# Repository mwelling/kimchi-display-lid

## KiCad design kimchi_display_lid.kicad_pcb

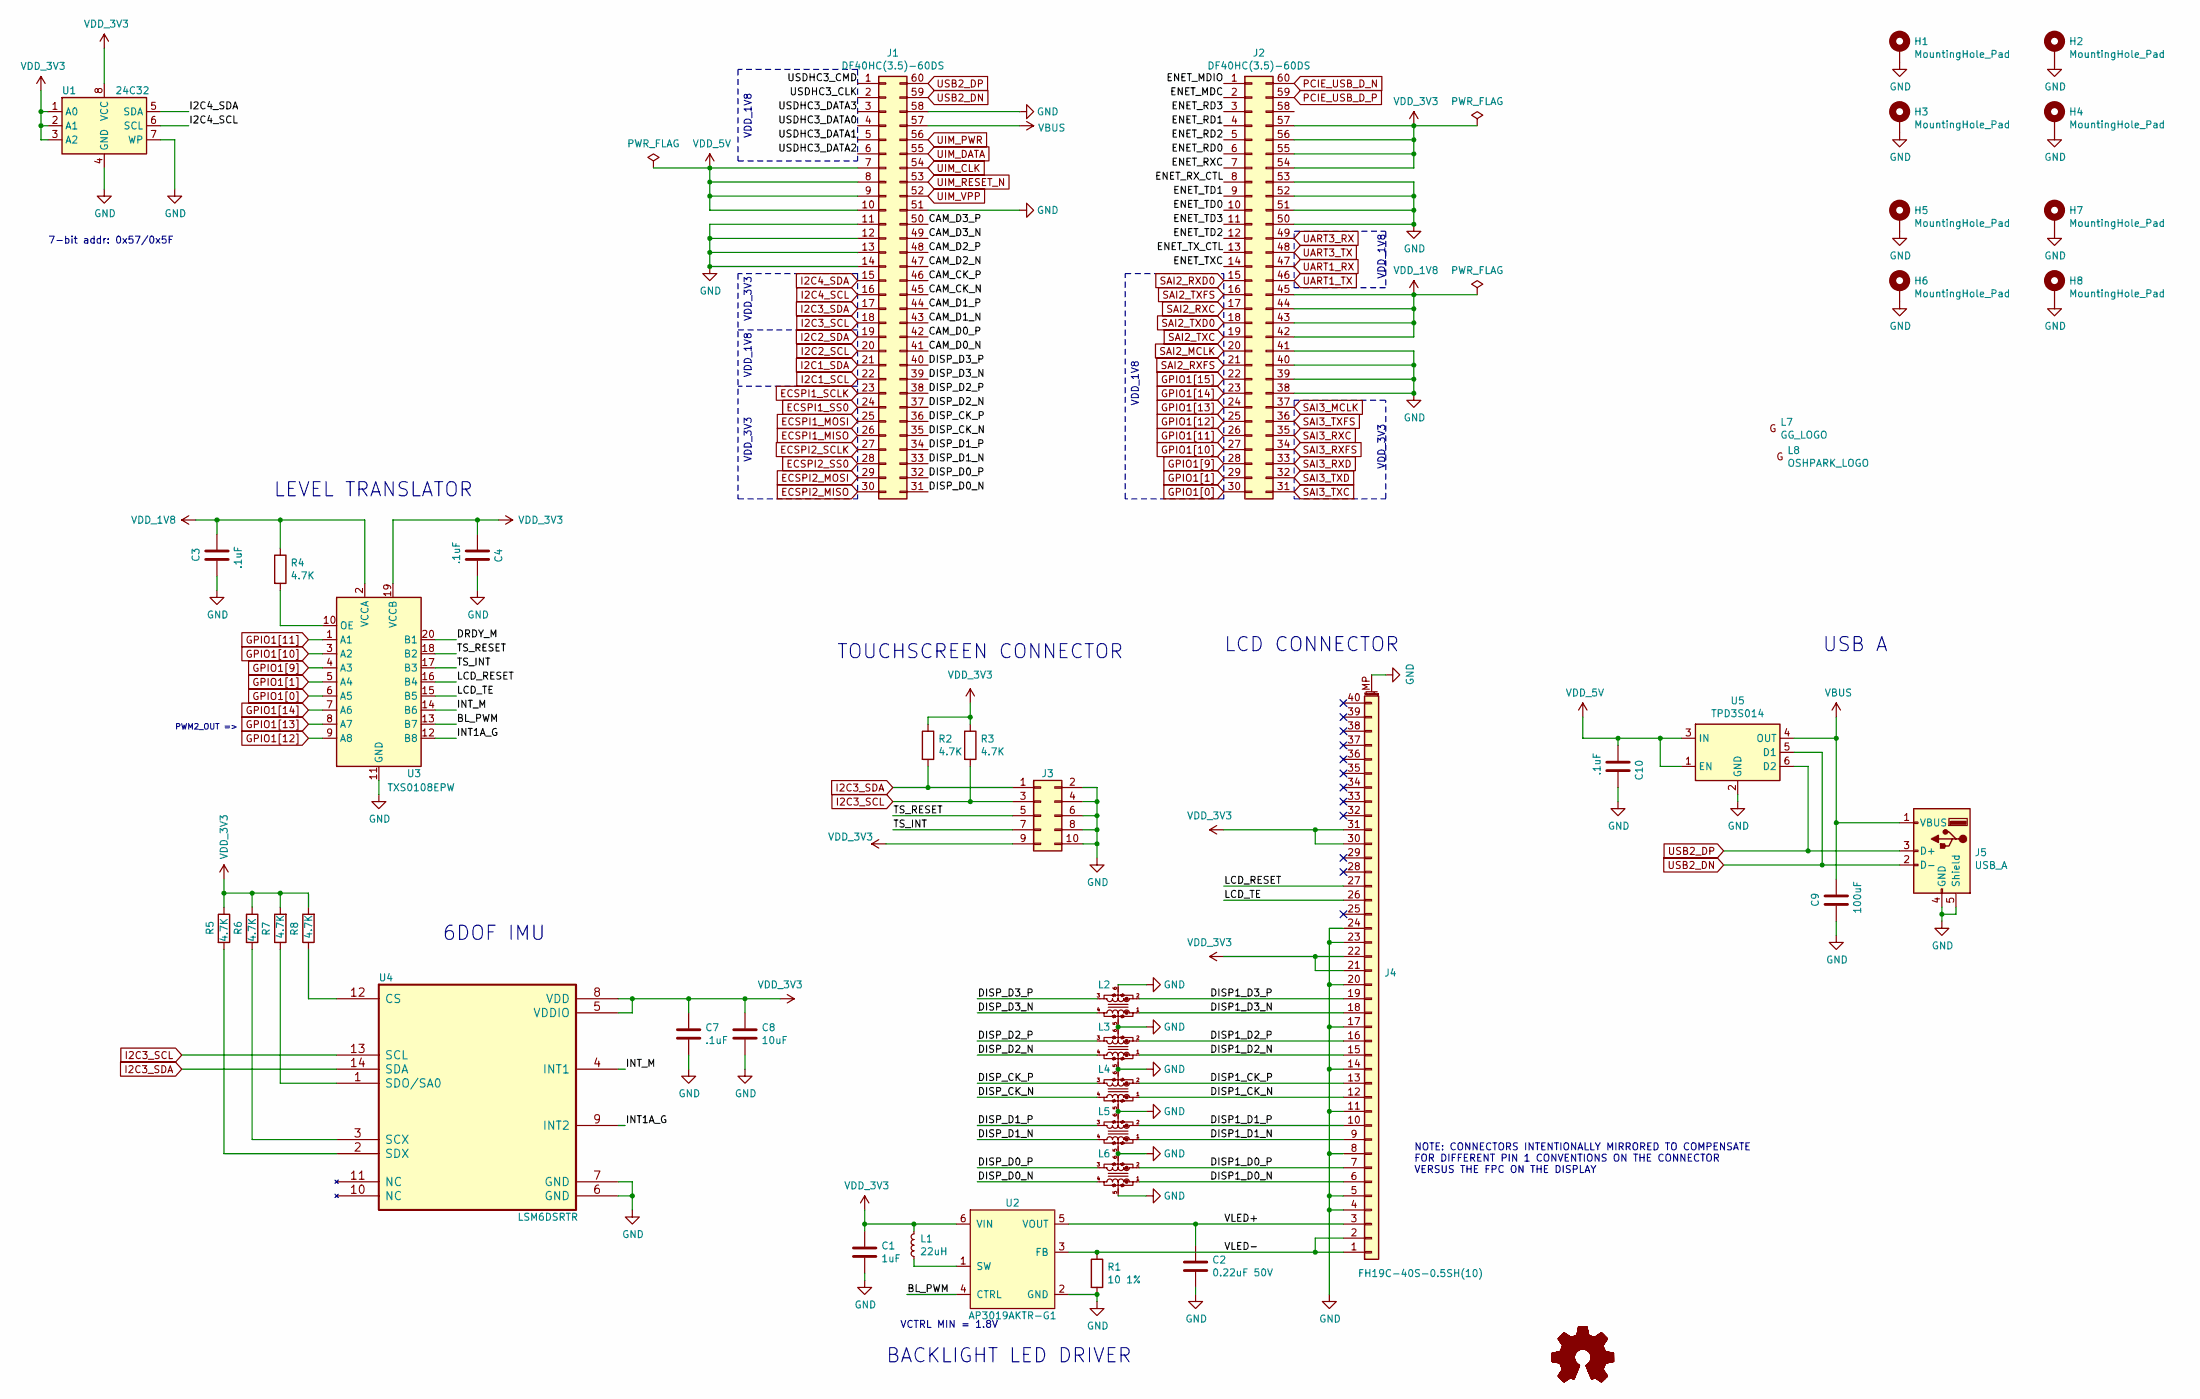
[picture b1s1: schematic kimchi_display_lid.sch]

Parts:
C1: 1uF; C_0603_1608Metric; Part C0603C105K4PAC7411
C2: 0.22uF 50V; C_0603_1608Metric; Part CGA3E3X7R1H224K080AB
C3, C4, C7, C10: .1uF; C_0603_1608Metric; Part C0603C104M5RACAUTO
C8: 10uF; C_0603_1608Metric; Part CL10A106MP8NNNC
C9: 100uF; C_1206_3216Metric; Part CC1206MKX5R5BB107
H1, H2, H3, H4, H5, H6, H7, H8: MountingHole_Pad; MountingHole_3mm_Pad
J1, J2: DF40HC(3.5)-60DS; Part DF40HC(3.5)-60DS
J3: Conn_02x05_Odd_Even; HIROSE_DF23C-10DS-0.5V(51)
J4: FH19C-40S-0.5SH(10); HRS_FH19C-40S-0.5SH_1x40-1MP_P0.50mm; Part FH19C-40S-0.5SH(10)
J5: USB_A; TE_1-292303-6; Part 1-292303-6
L1: 22uH; L_Taiyo-Yuden_MD-4040; Part TYA4012220M-10
L2, L3, L4, L5, L6: LCFE121002; Part LCFE121002
L7: GG_LOGO; groupgets_logo
L8: OSHPARK_LOGO; oshpark_logo
LOGO1: Logo_Open_Hardware_Small; OSHW-Logo_5.7x6mm_SilkScreen
LOGO2: Logo_Open_Hardware_Small; kimchi-micro-3d-model
LOGO3: Logo_Open_Hardware_Small; hoverboard-3d-model
R1: 10 1%; R_0603_1608Metric; Part RE0603FRE0710RL
R2, R3, R4, R5, R6, R7, R8: 4.7K; R_0603_1608Metric; Part RC0603JR-074K7L
U1: 24C32; DFN-8-1EP_3x2mm_P0.5mm_EP1.36x1.46mm; Part M24C32-FMC6TG
U2: AP3019AKTR-G1; SOT-23-6; Part AP3019AKTR-G1
U3: TXS0108EPW; TSSOP-20_4.4x6.5mm_P0.65mm; Part TXS0108EPW
U4: LSM6DSRTR
U5: TPD3S014; SOT-23-6; Part TPD3S014

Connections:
/BL_PWM: U2.4 (CTRL), U3.13 (B7)
/CAM_CK_N: J1.45
/CAM_CK_P: J1.46
/CAM_D0_N: J1.41
/CAM_D0_P: J1.42
/CAM_D1_N: J1.43
/CAM_D1_P: J1.44
/CAM_D2_N: J1.47
/CAM_D2_P: J1.48
/CAM_D3_N: J1.49
/CAM_D3_P: J1.50
/DISP1_CK_N: J4.12, L4.1
/DISP1_CK_P: J4.13, L4.2
/DISP1_D0_N: J4.6, L6.1
/DISP1_D0_P: J4.7, L6.2
/DISP1_D1_N: J4.9, L5.1
/DISP1_D1_P: J4.10, L5.2
/DISP1_D2_N: J4.15, L3.1
/DISP1_D2_P: J4.16, L3.2
/DISP1_D3_N: J4.18, L2.1
/DISP1_D3_P: J4.19, L2.2
/DISP_CK_N: J1.35, L4.4
/DISP_CK_P: J1.36, L4.3
/DISP_D0_N: J1.31, L6.4
/DISP_D0_P: J1.32, L6.3
/DISP_D1_N: J1.33, L5.4
/DISP_D1_P: J1.34, L5.3
/DISP_D2_N: J1.37, L3.4
/DISP_D2_P: J1.38, L3.3
/DISP_D3_N: J1.39, L2.4
/DISP_D3_P: J1.40, L2.3
/DRDY_M: U3.20 (B1)
/ENET_MDC: J2.2
/ENET_MDIO: J2.1
/ENET_RD0: J2.6
/ENET_RD1: J2.4
/ENET_RD2: J2.5
/ENET_RD3: J2.3
/ENET_RXC: J2.7
/ENET_RX_CTL: J2.8
/ENET_TD0: J2.10
/ENET_TD1: J2.9
/ENET_TD2: J2.12
/ENET_TD3: J2.11
/ENET_TXC: J2.14
/ENET_TX_CTL: J2.13
/INT1A_G: U3.12 (B8), U4.9 (INT2)
/INT_M: U3.14 (B6), U4.4 (INT1)
/LCD_RESET: J4.27, U3.16 (B4)
/LCD_TE: J4.26, U3.15 (B5)
/TS_INT: J3.7, U3.17 (B3)
/TS_RESET: J3.5, U3.18 (B2)
/USDHC3_CLK: J1.2
/USDHC3_CMD: J1.1
/USDHC3_DATA0: J1.4
/USDHC3_DATA1: J1.5
/USDHC3_DATA2: J1.6
/USDHC3_DATA3: J1.3
/VLED+: C2.1, J4.3, U2.5 (VOUT)
/VLED-: J4.1, J4.2, R1.1, U2.3 (FB)
ECSPI1_MISO: J1.26
ECSPI1_MOSI: J1.25
ECSPI1_SCLK: J1.23
ECSPI1_SS0: J1.24
ECSPI2_MISO: J1.30
ECSPI2_MOSI: J1.29
ECSPI2_SCLK: J1.27
ECSPI2_SS0: J1.28
GND: C1.2, C2.2, C3.2, C4.1, C7.2, C8.2, C9.2, C10.1, H1.1, H2.1, H3.1, H4.1, H5.1, H6.1, H7.1, H8.1, J1.11, J1.12, J1.13, J1.14, J1.51, J1.58, J2.38, J2.39, J2.40, J2.41, J2.50, J2.51, J2.52, J2.53, J3.2, J3.4, J3.6, J3.8, J3.10, J4.4, J4.5, J4.8, J4.11, J4.14, J4.17, J4.20, J4.23, J4.24, J4.MP (MountPin), J5.4 (GND), J5.5 (Shield), L2.5, L2.6 (5), L3.5, L3.6 (5), L4.5, L4.6 (5), L5.5, L5.6 (5), L6.5, L6.6 (5), R1.2, U1.4 (GND), U1.7 (WP), U2.2 (GND), U3.11 (GND), U4.6 (GND), U4.7 (GND), U5.2 (GND)
GPIO1[0]: J2.30, U3.6 (A5)
GPIO1[1]: J2.29, U3.5 (A4)
GPIO1[9]: J2.28, U3.4 (A3)
GPIO1[10]: J2.27, U3.3 (A2)
GPIO1[11]: J2.26, U3.1 (A1)
GPIO1[12]: J2.25, U3.9 (A8)
GPIO1[13]: J2.24, U3.8 (A7)
GPIO1[14]: J2.23, U3.7 (A6)
GPIO1[15]: J2.22
I2C1_SCL: J1.22
I2C1_SDA: J1.21
I2C2_SCL: J1.20
I2C2_SDA: J1.19
I2C3_SCL: J1.18, J3.3, R3.2, U4.13 (SCL)
I2C3_SDA: J1.17, J3.1, R2.2, U4.14 (SDA)
I2C4_SCL: J1.16, U1.6 (SCL)
I2C4_SDA: J1.15, U1.5 (SDA)
unnamed: L1.1, U2.1 (SW)
unnamed: R4.2, U3.10 (OE)
unnamed: R5.2, U4.2 (SDX)
unnamed: R6.2, U4.3 (SCX)
unnamed: R7.1, U4.1 (SDO/SA0)
unnamed: R8.1, U4.12 (CS)
PCIE_USB_D_N: J2.60
PCIE_USB_D_P: J2.59
SAI2_MCLK: J2.20
SAI2_RXC: J2.17
SAI2_RXD0: J2.15
SAI2_RXFS: J2.21
SAI2_TXC: J2.19
SAI2_TXD0: J2.18
SAI2_TXFS: J2.16
SAI3_MCLK: J2.37
SAI3_RXC: J2.35
SAI3_RXD: J2.33
SAI3_RXFS: J2.34
SAI3_TXC: J2.31
SAI3_TXD: J2.32
SAI3_TXFS: J2.36
UART1_RX: J2.47
UART1_TX: J2.46
UART3_RX: J2.49
UART3_TX: J2.48
UIM_CLK: J1.54
UIM_DATA: J1.55
UIM_PWR: J1.56
UIM_RESET_N: J1.53
UIM_VPP: J1.52
USB2_DN: J1.59, J5.2 (D-), U5.5 (D1)
USB2_DP: J1.60, J5.3 (D+), U5.6 (D2)
VBUS: C9.1, J1.57, J5.1 (VBUS), U5.4 (OUT)
VDD_1V8: C3.1, J2.42, J2.43, J2.44, J2.45, R4.1, U3.2 (VCCA)
VDD_3V3: C1.1, C4.2, C7.1, C8.1, J2.54, J2.55, J2.56, J2.57, J3.9, J4.21, J4.22, J4.30, J4.31, L1.2, R2.1, R3.1, R5.1, R6.1, R7.2, R8.2, U1.1 (A0), U1.2 (A1), U1.3 (A2), U1.8 (VCC), U2.6 (VIN), U3.19 (VCCB), U4.5 (VDDIO), U4.8 (VDD)
VDD_5V: C10.2, J1.7, J1.8, J1.9, J1.10, U5.1 (EN), U5.3 (IN)

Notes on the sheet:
7-bit addr: 0x57/0x5F
VDD_1V8
VDD_3V3
BACKLIGHT LED DRIVER
VCTRL MIN = 1.8V
TOUCHSCREEN CONNECTOR
LCD CONNECTOR
NOTE: CONNECTORS INTENTIONALLY MIRRORED TO COMPENSATE FOR DIFFERENT PIN 1 CONVENTIONS ON THE CONNECTOR VERSUS THE FPC ON THE DISPLAY
LEVEL TRANSLATOR
PWM2_OUT =>
USB A
6DOF IMU

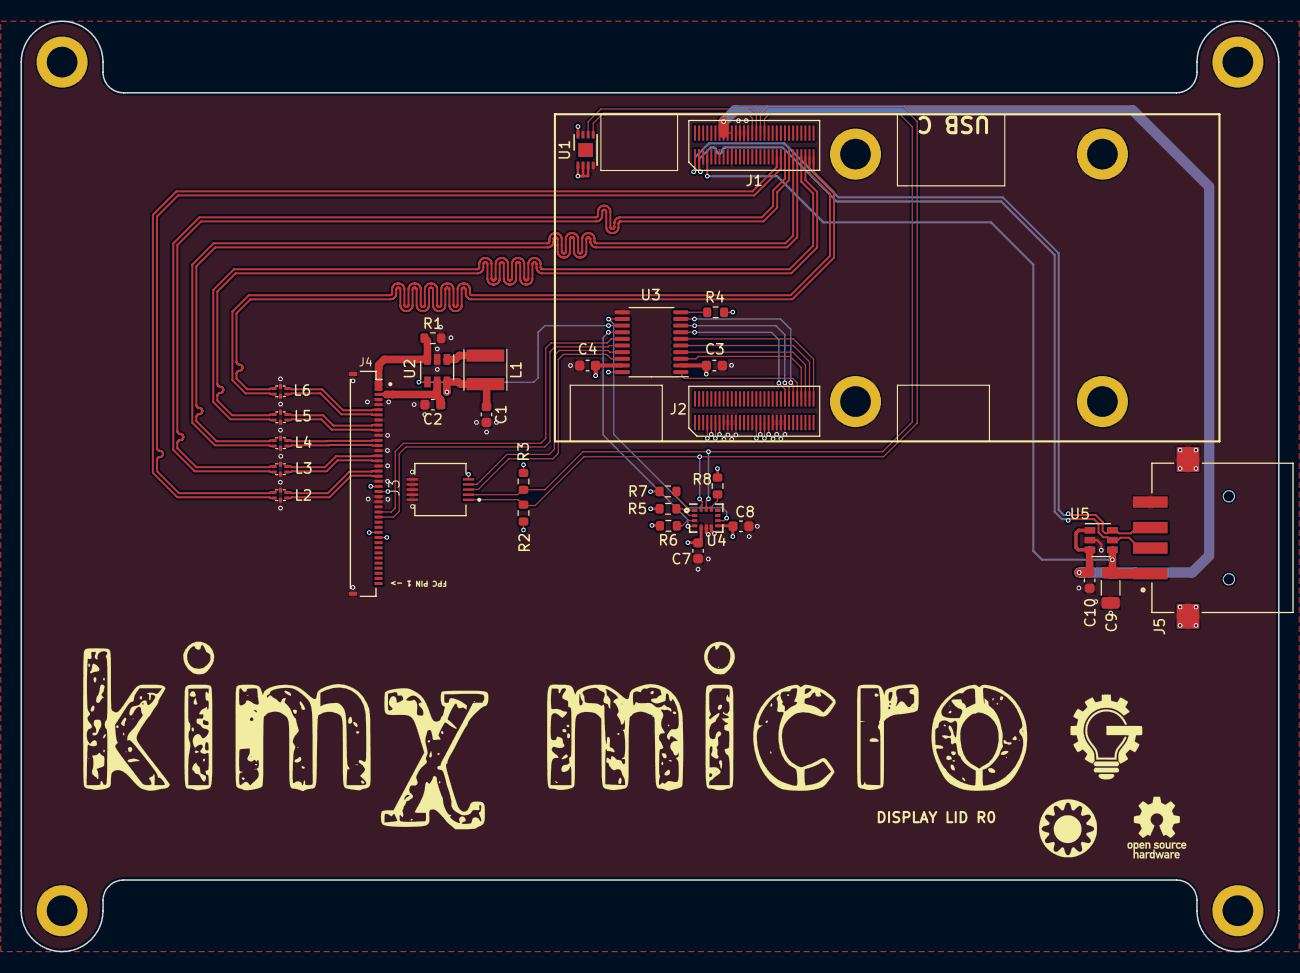
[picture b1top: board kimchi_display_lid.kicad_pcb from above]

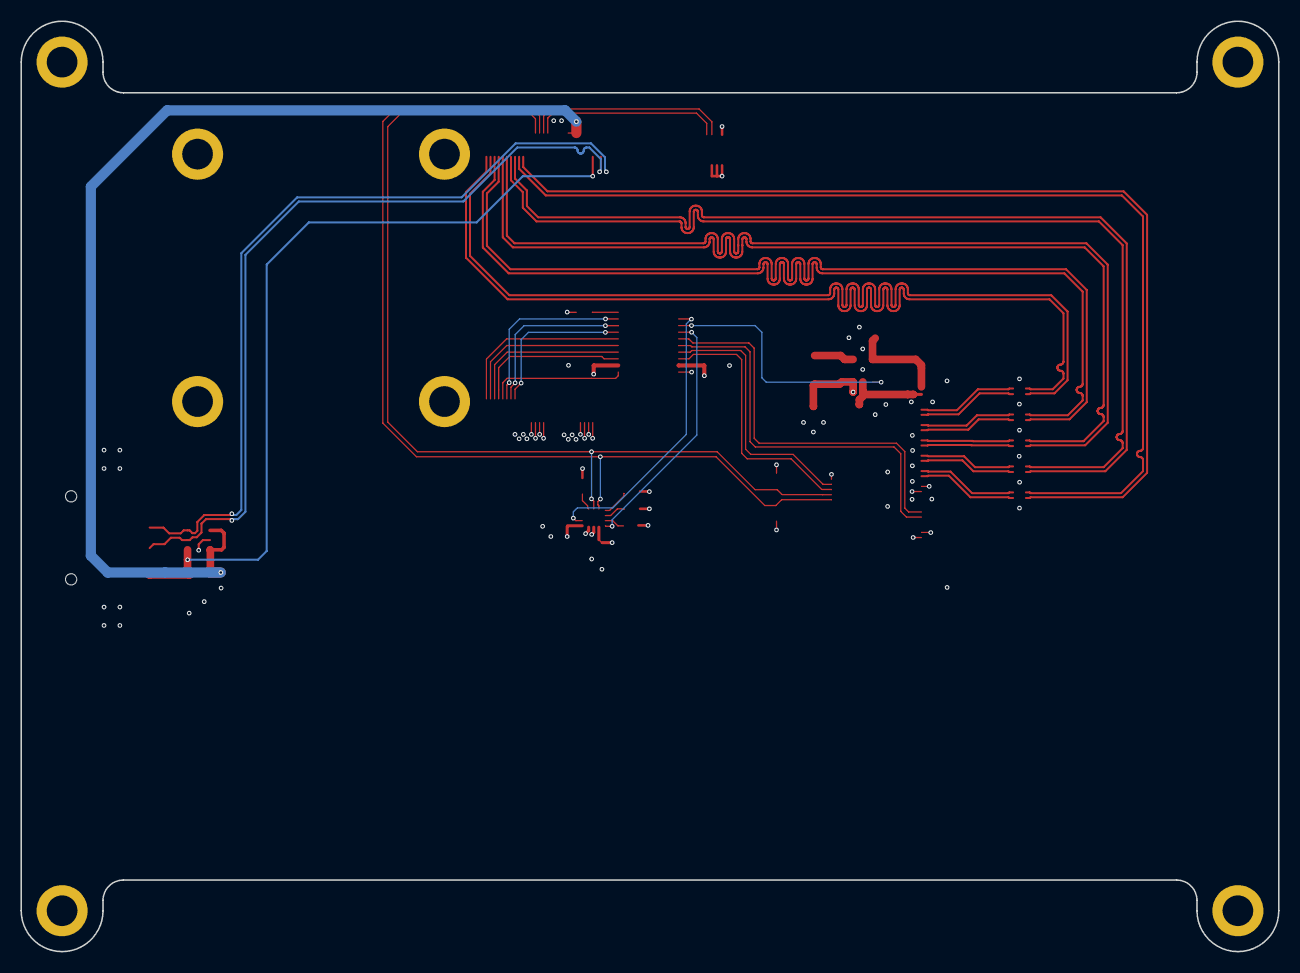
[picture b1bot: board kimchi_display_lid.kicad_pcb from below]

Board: 4 copper layers, 123.0 x 91.0 mm, 45 parts (8 on the bottom side), 54 nets.

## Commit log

2020-12-14 Clean up
2020-12-14 Add board outline
2020-12-14 Add datasheet for screen
2020-12-14 Add 3D model for the kimchi micro
    The PEMs are supposed to be 3.5mm but the spacing is enforced in the footprint.
2020-12-14 Put 3D model in PCB
    For virtual fitment checks :)
2020-12-14 Add LCD backlight LED driver
2020-12-14 Bump inductor to a big package
2020-12-14 Add some manufacturer part numbers
    So I don't forget them. ;)
2020-12-14 OCD fixes
2020-12-14 Add connectors for the LCD and touchscreen
    May need a level translator for the misc signals
2020-12-14 Add LCD connectors to the schematic / PCB
2020-12-15 Intentionally mirror the connections to FPC
    The pin 1 orientation of the FPC is opposite of the connector.
2020-12-15 Update placement of FPC connectors and kimx module
    Should be close enough.
2020-12-20 Add level translator and route
2020-12-20 Add USB connector
2020-12-20 Move USB to opposite side of PCB
    It was in the way of the LCD cable on the other side. Doh!
2020-12-20 Connect USB sheild to GND
2020-12-20 Add 9DOF IMU
2020-12-20 Tweaky tweaks
2020-12-23 Add ESD protection and filtering to USB and DSI
2020-12-23 Fix symbol for common mode choke
2020-12-25 Whooops PWM is on GPIO1_13
2021-01-13 Move the mounting holes to avoid blocking LCD FPC
    Also removes a bit length on the board to compensate for
    the cable wrapping around the PCB.
    May have to move the touchsreen connector and use an adapter
    to add length.
2021-01-13 Add part numbers to the schematic for BOM export
2021-01-21 IMU Changed
    9DOF IMU is out of stock, added new IMU that is 6DOF adjusted PCB design to include new IMU.
2021-01-25 Logos
    added logots
2021-01-31 Add a small board to connect touchscreen
    When the cables wrap around the PCB the distance between
    the 40pin and 6pin connectors is too close.
    The "hoverboard" floats over the 40pin connector to
    air jordan the 6pin down to the main board via a stacked
    connector pair.
2021-02-03 Totally messed up the connections to the hoverboard
    Great scott!!
    Only caught this after placing an order at OSHpark.
    Swiftly cancelled for this fix.
2021-02-05 Add some silkscreen flare
